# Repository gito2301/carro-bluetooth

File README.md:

# carro-bluetooth V0.1

# Lista de materiales
* Arduino UNO
* 1 x L293D (Puente H)
* 2 x Motores con rueda
* 1 x Resistencia 1K
* 1 x Resistencia 2.2K
* Módulo bluetooth HC-05
* Portabatería de 4 puestos
* 4 baterías alcalinas (de 1.5v, otras no serán suficiente para dar potencia a los motores)
* Base para ensamblar el carro

# Circuito

# Programación Arduino

El código para programar nuestro arduino está al interior de la carpeta arduino

# APP Android

Al interior de la carpeta android, se encuentra un proyecto simple con la aplicación de android para enviar al motor instrucciones simples de ir hacia adelante, atrás, izquierda, derecha y detenerse.

Para instalar el apk que allí reside, debe habilitarse el modo desarrollador (proceso que depende de cada celular).

# Referencias

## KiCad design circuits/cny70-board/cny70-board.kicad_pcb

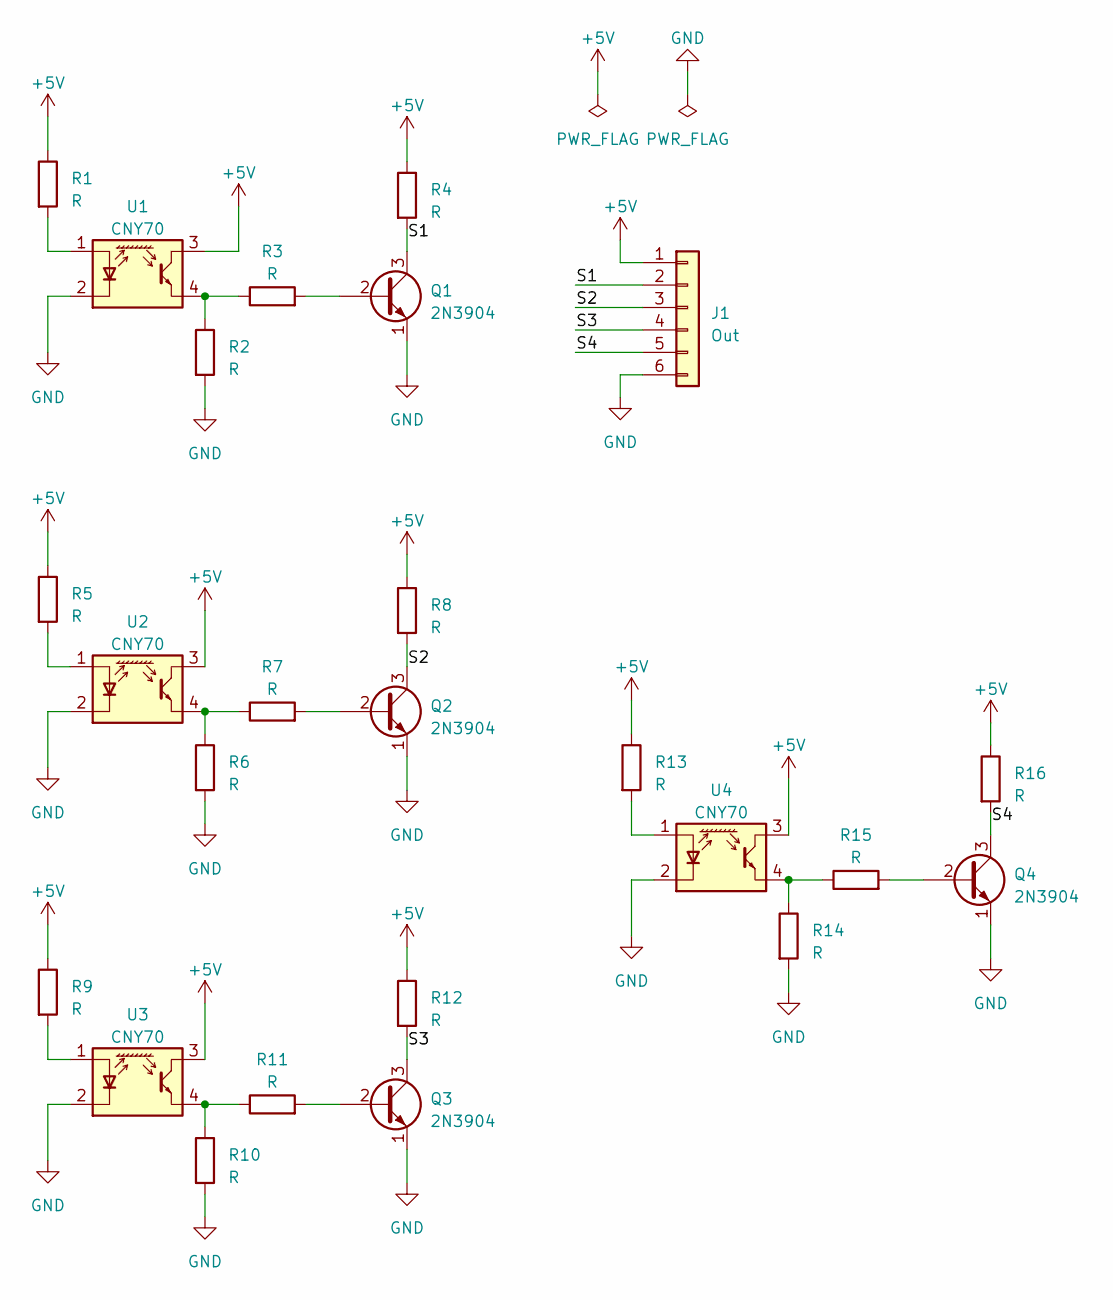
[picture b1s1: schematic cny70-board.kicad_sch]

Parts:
J1: Out; PinHeader_1x06_P2.00mm_Vertical
Q1, Q2, Q3, Q4: 2N3904; TO-92_Inline_Wide
R1, R2, R3, R4, R5, R6, R7, R8, R9, R10, R11, R12, R13, R14, R15, R16: R; R_Axial_DIN0207_L6.3mm_D2.5mm_P7.62mm_Horizontal
U1, U2, U3, U4: CNY70; Vishay_CNY70

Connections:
+5V: J1.1, R1.1, R4.1, R5.1, R8.1, R9.1, R12.1, R13.1, R16.1, U1.3 (C), U2.3 (C), U3.3 (C), U4.3 (C)
/S1: J1.2, Q1.3 (C), R4.2
/S2: J1.3, Q2.3 (C), R8.2
/S3: J1.4, Q3.3 (C), R12.2
/S4: J1.5, Q4.3 (C), R16.2
GND: J1.6, Q1.1 (E), Q2.1 (E), Q3.1 (E), Q4.1 (E), R2.2, R6.2, R10.2, R14.2, U1.2 (K), U2.2 (K), U3.2 (K), U4.2 (K)
unnamed: Q1.2 (B), R3.2
unnamed: Q2.2 (B), R7.2
unnamed: Q3.2 (B), R11.2
unnamed: Q4.2 (B), R15.2
unnamed: R1.2, U1.1 (A)
unnamed: R2.1, R3.1, U1.4 (E)
unnamed: R5.2, U2.1 (A)
unnamed: R6.1, R7.1, U2.4 (E)
unnamed: R9.2, U3.1 (A)
unnamed: R10.1, R11.1, U3.4 (E)
unnamed: R13.2, U4.1 (A)
unnamed: R14.1, R15.1, U4.4 (E)

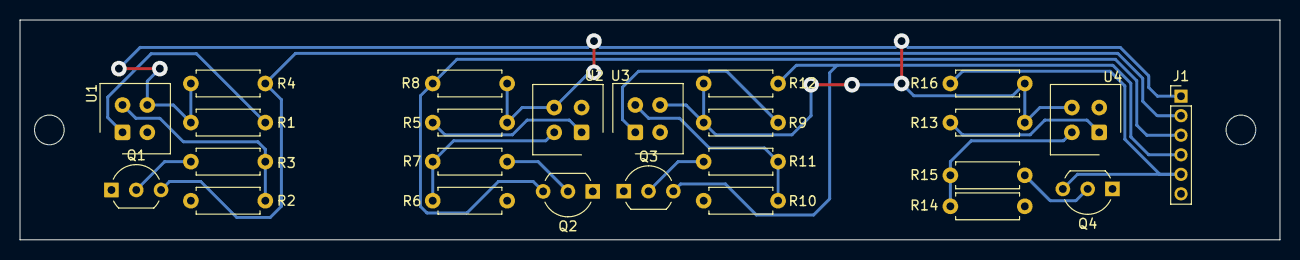
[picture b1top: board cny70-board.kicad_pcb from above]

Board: 2 copper layers, 129.0 x 22.5 mm, 25 parts (0 on the bottom side), 18 nets.

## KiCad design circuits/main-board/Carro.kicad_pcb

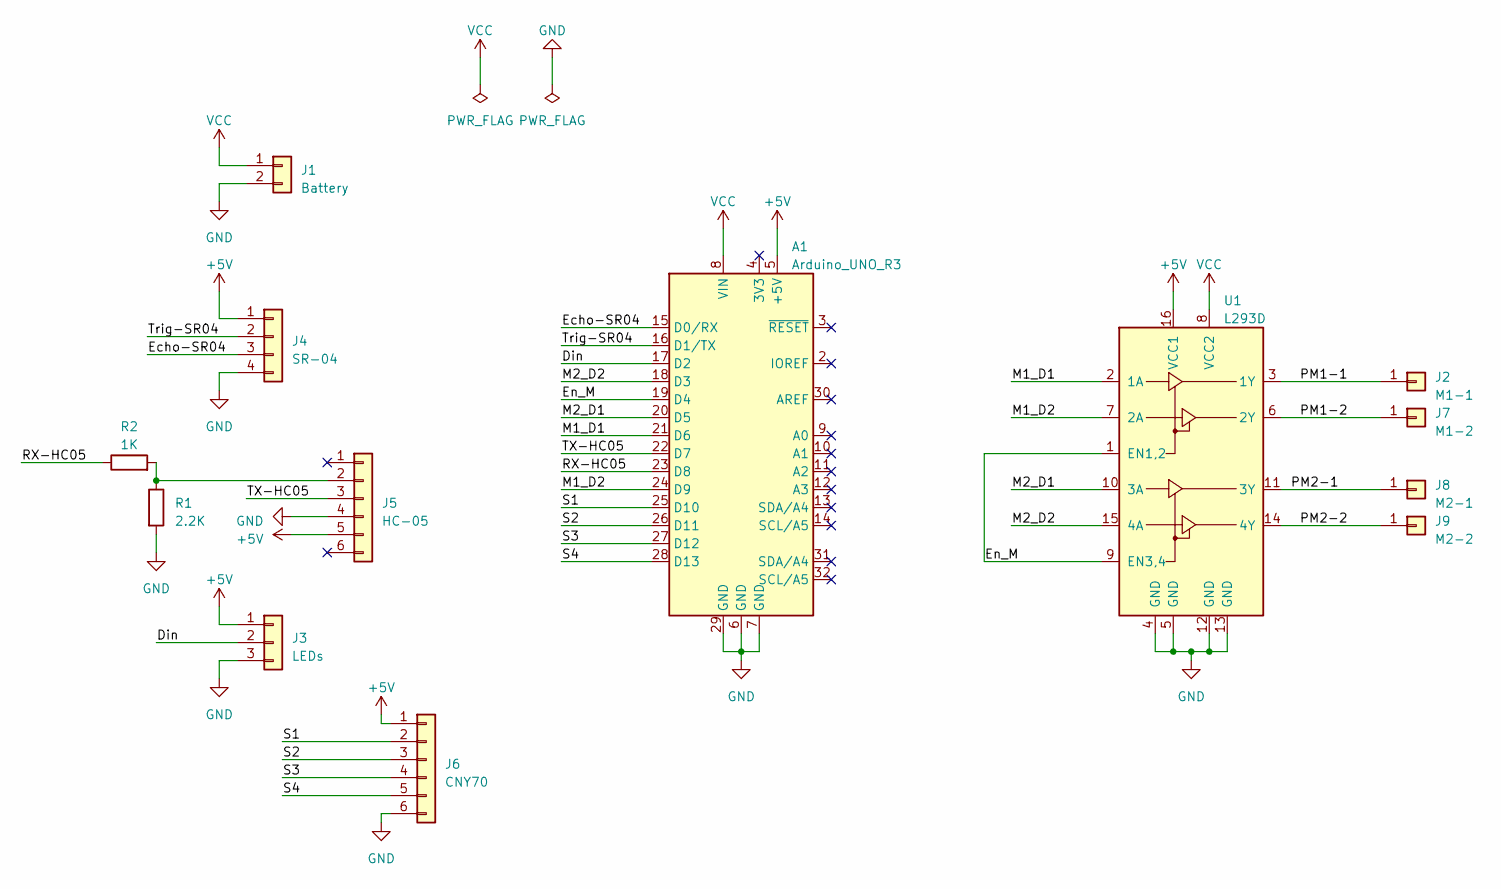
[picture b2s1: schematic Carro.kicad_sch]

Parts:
A1: Arduino_UNO_R3; Arduino_UNO_R3-pins
J1: Battery; PinHeader_1x02_P2.54mm_Vertical
J2: M1-1; PinHeader_1x01_P1.00mm_Horizontal
J3: LEDs; PinHeader_1x03_P2.54mm_Vertical
J4: SR-04; PinSocket_1x04_P2.54mm_Vertical
J5: HC-05; PinSocket_1x06_P2.54mm_Vertical
J6: CNY70; PinHeader_1x06_P2.54mm_Vertical
J7: M1-2; PinHeader_1x01_P1.00mm_Horizontal
J8: M2-1; PinHeader_1x01_P1.00mm_Horizontal
J9: M2-2; PinHeader_1x01_P1.00mm_Horizontal
R1: 2.2K; R_Axial_DIN0207_L6.3mm_D2.5mm_P7.62mm_Horizontal
R2: 1K; R_Axial_DIN0207_L6.3mm_D2.5mm_P7.62mm_Horizontal
U1: L293D; DIP-16_W7.62mm

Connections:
+5V: A1.5 (+5V), J3.1, J4.1, J5.5, J6.1, U1.16 (VCC1)
/Din: A1.17 (D2), J3.2
/Echo-SR04: A1.15 (D0/RX), J4.3
/En_M: A1.19 (D4), U1.1 (EN1,2), U1.9 (EN3,4)
/M1_D1: A1.21 (D6), U1.2 (1A)
/M1_D2: A1.24 (D9), U1.7 (2A)
/M2_D1: A1.20 (D5), U1.10 (3A)
/M2_D2: A1.18 (D3), U1.15 (4A)
/PM1-1: J2.1, U1.3 (1Y)
/PM1-2: J7.1, U1.6 (2Y)
/PM2-1: J8.1, U1.11 (3Y)
/PM2-2: J9.1, U1.14 (4Y)
/RX-HC05: A1.23 (D8), R2.1
/S1: A1.25 (D10), J6.2
/S2: A1.26 (D11), J6.3
/S3: A1.27 (D12), J6.4
/S4: A1.28 (D13), J6.5
/TX-HC05: A1.22 (D7), J5.3
/Trig-SR04: A1.16 (D1/TX), J4.2
GND: A1.6 (GND), A1.7 (GND), A1.29 (GND), J1.2, J3.3, J4.4, J5.4, J6.6, R1.2, U1.4 (GND), U1.5 (GND), U1.12 (GND), U1.13 (GND)
unnamed: J5.2, R1.1, R2.2
VCC: A1.8 (VIN), J1.1, U1.8 (VCC2)

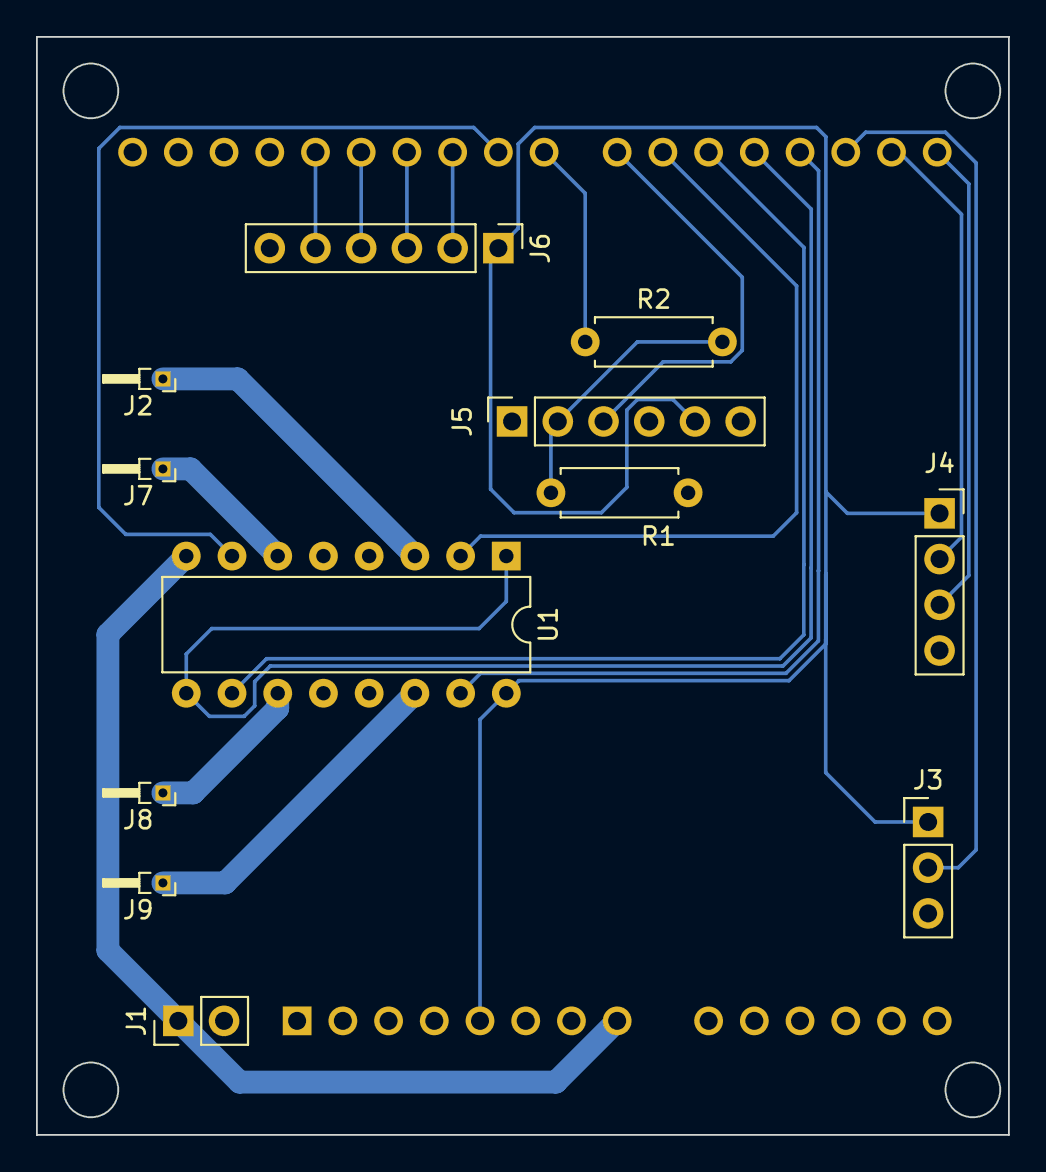
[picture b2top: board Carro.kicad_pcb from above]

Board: 2 copper layers, 54.0 x 61.0 mm, 13 parts (1 on the bottom side), 22 nets.

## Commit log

2022-06-06 base code
    First commit with the base code.
2023-05-10 First PCB Design
    Simple circuit design to use Arduino UNO with cny70, SR04, HC05, two motors with L293D and a led strip WS2812B.
2023-06-16 New CNY70 board
    Changes in tracks and spacings to match new configuration on CNC.
2023-06-19 Grb and Drl for CNY70 board - V0.1
    Grb and Drl for CNY70 board - V0.1
2023-06-19 Line width changed
    Path/spaces are now 0.3048/0.3048 mm (12/12 mil), and vias are 1.6-0.8 mm
